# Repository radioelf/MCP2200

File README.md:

# MCP2200
Software and hardware for Microchip's MCP2200 IC and control of 4 SSR relays.

Creative Commons License Disclaimer
UNLESS OTHERWISE MUTUALLY AGREED TO BY THE PARTIES AND MAKES NO REPRESENTATIONS OR WARRANTIES OF ANY STATUTORY OR OTHERWISE, INCLUDING, WITHOUT LIMITAT FITNESS FOR A PARTICULAR PURPOSE, NONINFRINGEMENT, ACCURACY, OR THE PRESENCE OF ABSENCE OF ERRORS, WH DO NOT ALLOW THE EXCLUSION OF IMPLIED WARRANTIES, EXCEPT TO THE EXTENT REQUIRED BY APPLICABLE LAW, I ON ANY LEGAL THEORY FOR ANY SPECIAL, INCIDENTAL, C ARISING OUT OF THIS LICENSE OR THE USE OF THE WORK POSSIBILITY OF SUCH DAMAGES.

http://creativecommons.org/licenses/by-sa/3.0/

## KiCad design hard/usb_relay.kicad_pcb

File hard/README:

PCB for MCP2200 and SSR 
Application: KiCad

Version: 6.99.0-unknown-492e6548ff~162~ubuntu22.04.1, release build

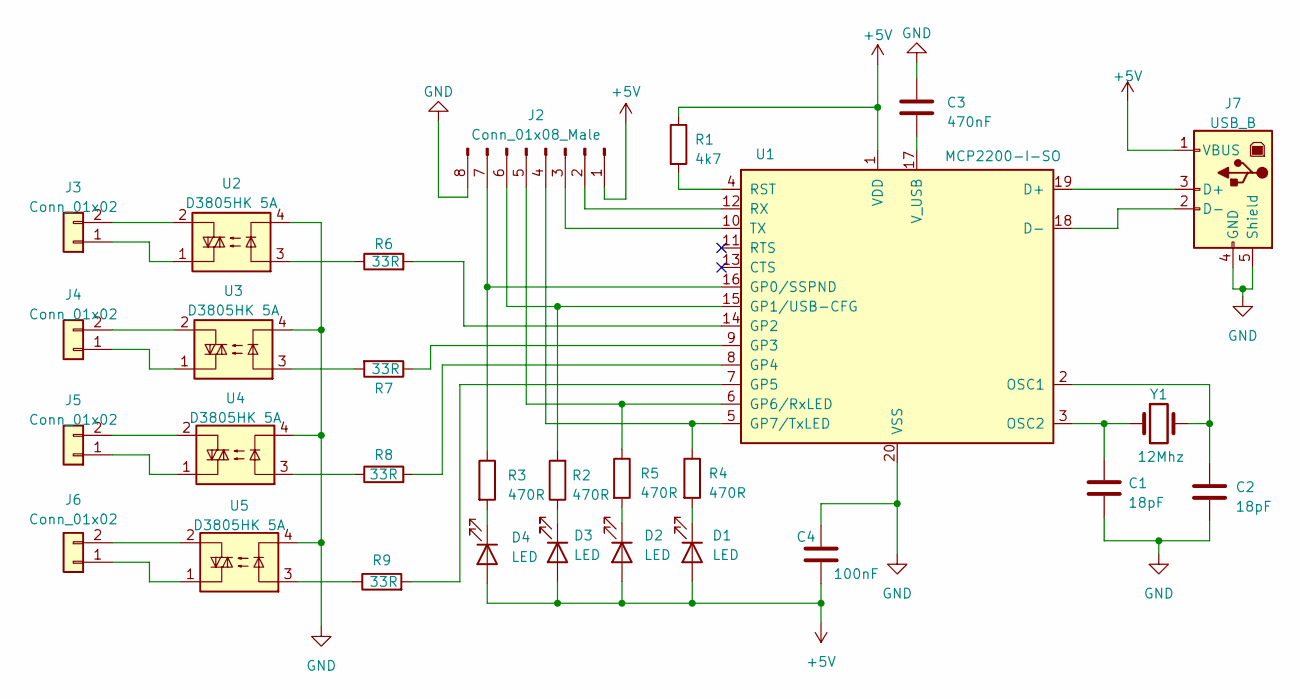
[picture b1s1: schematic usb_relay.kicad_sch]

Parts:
C1, C2: 18pF; C_0805_2012Metric
C3: 470nF; C_1206_3216Metric
C4: 100nF; C_1206_3216Metric
D1, D2, D3, D4: LED; LED_1206_3216Metric
J2: Conn_01x08_Male; TerminalBlock_4Ucon_1x08_P3.50mm_Horizontal
J3, J4, J5, J6: Conn_01x02; PhoenixContact_GMSTBVA_2,5_2-G_1x02_P7.50mm_Vertical
J7: USB_B; USB_B_Lumberg_2411_02_Horizontal
R1: 4k7; R_0805_2012Metric
R2, R3, R4, R5: 470R; R_0805_2012Metric
R6, R7, R8, R9: 33R; R_0805_2012Metric
U1: MCP2200-I-SO; SSOP-20_5.3x7.2mm_P0.65mm
U2, U3, U4, U5: D3805HK 5A; Relay_SSR_D3805HK
Y1: 12Mhz; Crystal_HC18-U_Vertical

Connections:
+5V: C4.2, D1.2 (A), D2.2 (A), D3.2 (A), D4.2 (A), J2.1, J7.1 (VBUS), R1.1, U1.1 (VDD)
GND: C1.2, C2.2, C3.1, C4.1, J2.8, J7.4 (GND), J7.5 (Shield), U1.20 (VSS), U2.4, U3.4, U4.4, U5.4
unnamed: D1.1 (K), R4.2
unnamed: D2.1 (K), R5.2
unnamed: D3.1 (K), R2.1
unnamed: D4.1 (K), R3.2
unnamed: J2.2, U1.12 (RX)
unnamed: J2.3, U1.10 (TX)
unnamed: J2.4, R4.1, U1.5 (GP7/TxLED)
unnamed: J2.5, R5.1, U1.6 (GP6/RxLED)
unnamed: J2.6, R2.2, U1.15 (GP1/USB-CFG)
unnamed: J2.7, R3.1, U1.16 (GP0/SSPND)
unnamed: J3.1, U2.1
unnamed: J3.2, U2.2
unnamed: J4.1, U3.1
unnamed: J4.2, U3.2
unnamed: J5.1, U4.1
unnamed: J5.2, U4.2
unnamed: J6.1, U5.1
unnamed: J6.2, U5.2
unnamed: J7.3 (D+), U1.19 (D+)
unnamed: J7.2 (D-), U1.18 (D-)
unnamed: R6.1, U2.3
unnamed: R7.2, U3.3
unnamed: R8.1, U4.3
unnamed: R9.1, U5.3
unnamed: R6.2, U1.14 (GP2)
unnamed: R7.1, U1.9 (GP3)
unnamed: R8.2, U1.8 (GP4)
unnamed: R9.2, U1.7 (GP5)
unnamed: C2.1, U1.2 (OSC1), Y1.2
unnamed: C1.1, U1.3 (OSC2), Y1.1
unnamed: R1.2, U1.4 (RST)
unnamed: C3.2, U1.17 (V_USB)

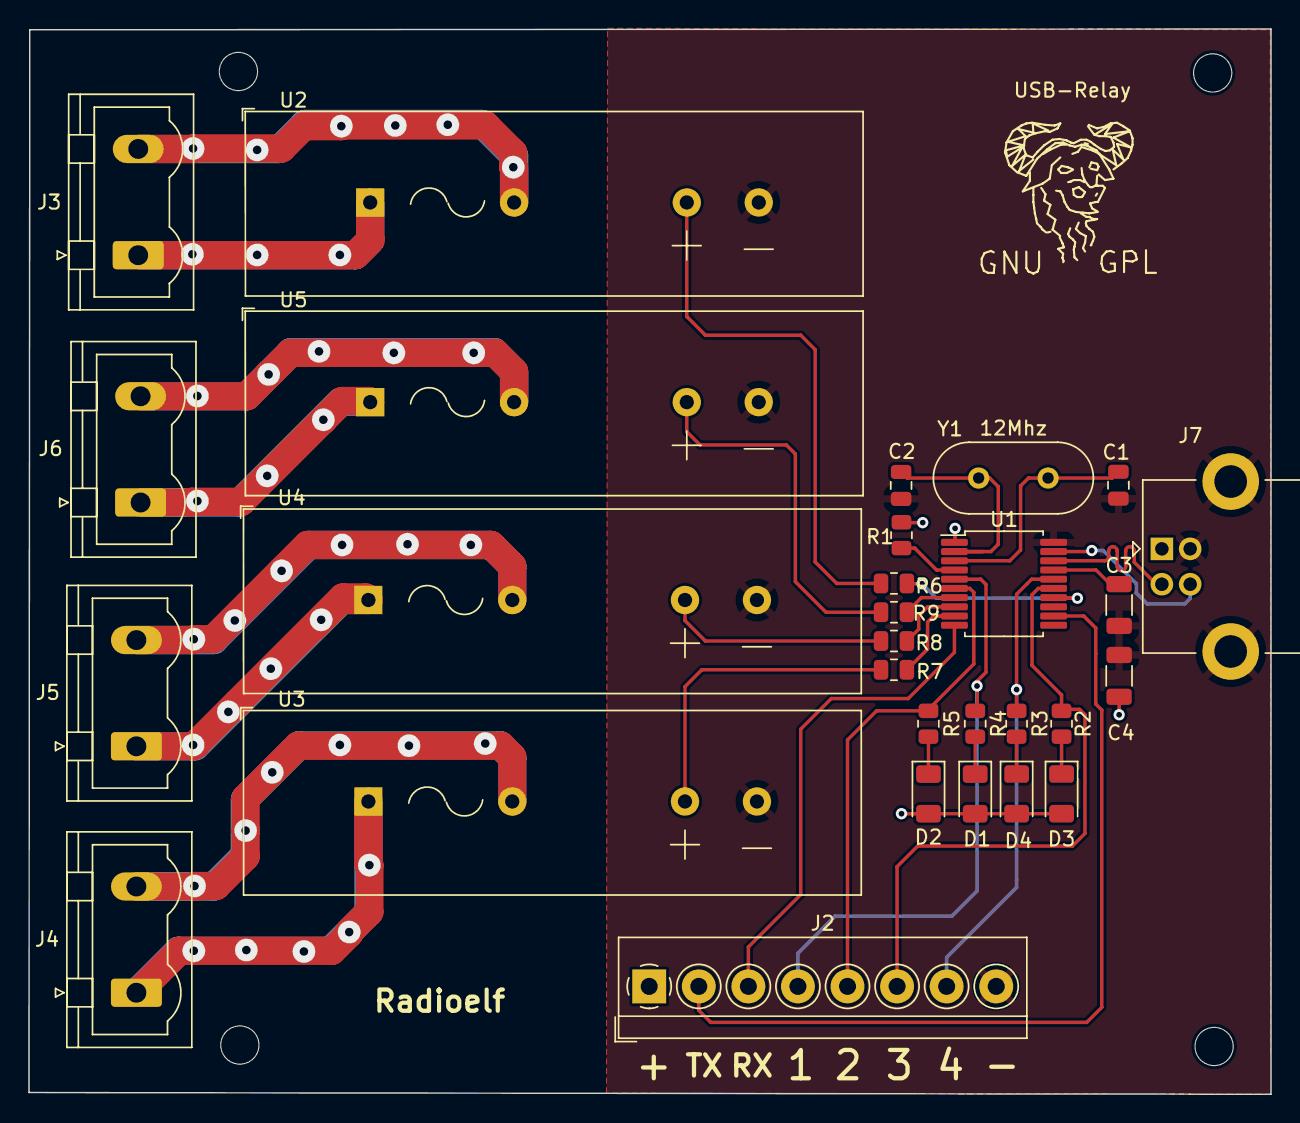
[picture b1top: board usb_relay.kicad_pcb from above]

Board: 2 copper layers, 87.7 x 75.2 mm, 30 parts (0 on the bottom side), 34 nets.

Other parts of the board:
USB-Relay: Symbol_GNU-Logo_SilkscreenTop
